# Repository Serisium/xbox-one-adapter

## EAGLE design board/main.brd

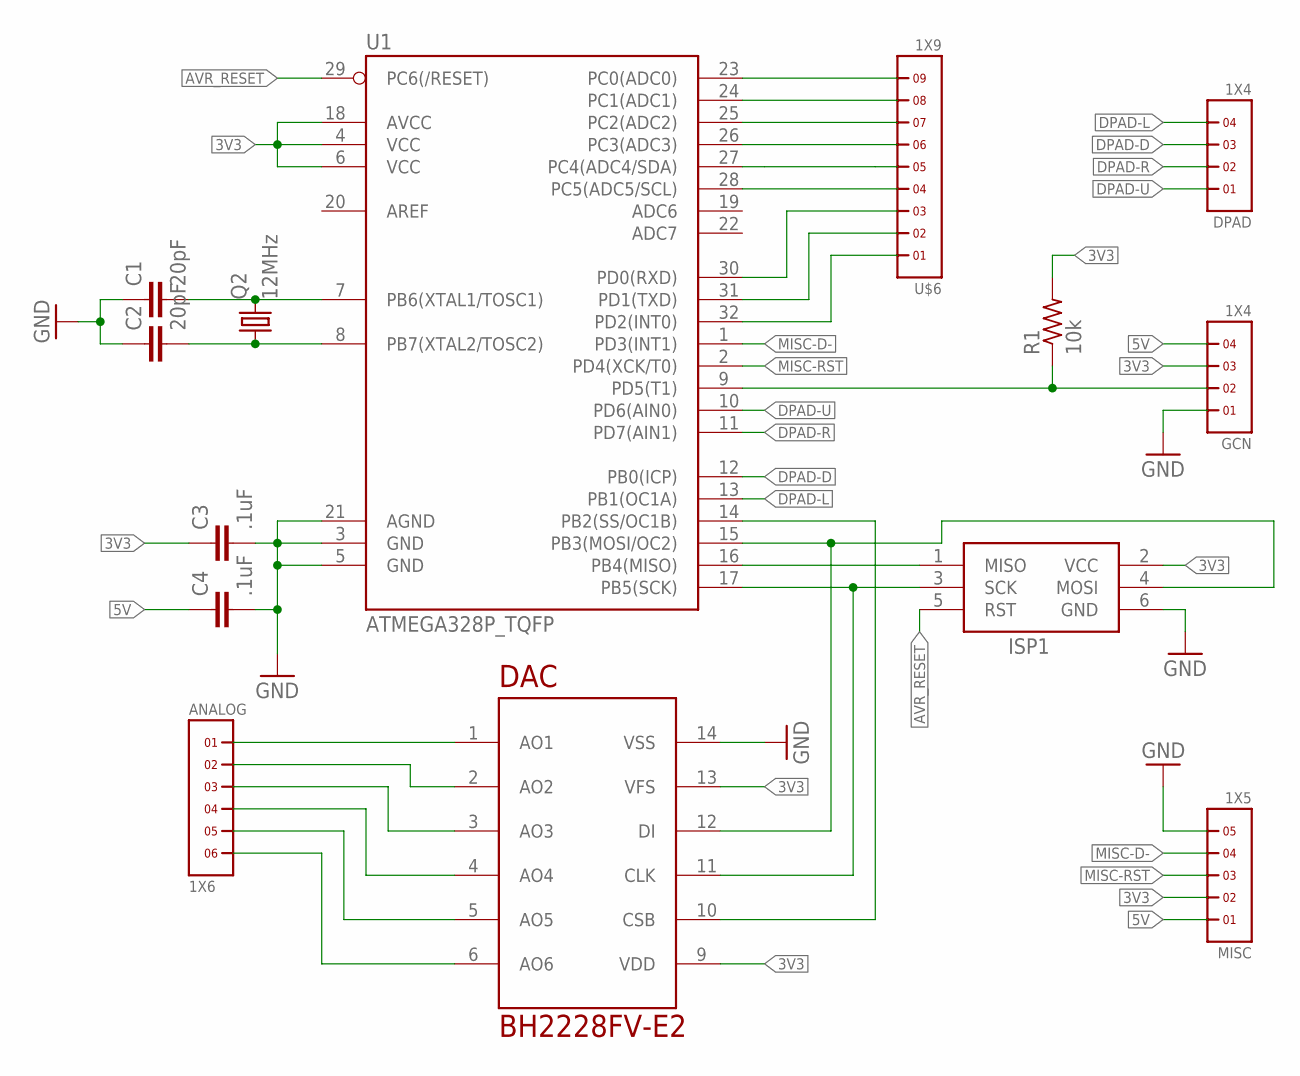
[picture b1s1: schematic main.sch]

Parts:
ANALOG: 1X6
C1, C2: 20pF; C0603
C3, C4: .1uF; C0603
DAC: BH2228FV-E2; TSSOP14
DPAD: 1X4
GCN: 1X4
ISP1: AVRISP-6; AVRISP
MISC: 1X5
Q2: 12MHz; HC49/S
R1: 10k; R0603
U1: ATMEGA328P_TQFP; TQFP32-08
U$6: 1X9

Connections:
3V3: C3.1, DAC.9 (VDD), DAC.13 (VFS), GCN.3, ISP1.2 (VCC), MISC.2, R1.2, U1.4 (VCC), U1.6 (VCC), U1.18 (AVCC)
5V: C4.1, GCN.4, MISC.1
A: U1.23 (PC0(ADC0)), U$6.9
AVR_RESET: ISP1.5 (RST), U1.29 (PC6(/RESET))
B: U1.24 (PC1(ADC1)), U$6.8
DPAD-D: DPAD.3, U1.12 (PB0(ICP))
DPAD-L: DPAD.4, U1.13 (PB1(OC1A))
DPAD-R: DPAD.2, U1.11 (PD7(AIN1))
DPAD-U: DPAD.1, U1.10 (PD6(AIN0))
GCN_SIG: GCN.2, R1.1, U1.9 (PD5(T1))
GND: C1.1, C2.1, C3.2, C4.2, DAC.14 (VSS), GCN.1, ISP1.6 (GND), MISC.5, U1.3 (GND), U1.5 (GND), U1.21 (AGND)
L: U1.27 (PC4(ADC4/SDA)), U$6.5
MENU: U1.30 (PD0(RXD)), U$6.3
MISC-D-: MISC.4, U1.1 (PD3(INT1))
MISC-RST: MISC.3, U1.2 (PD4(XCK/T0))
MOSI: DAC.12 (DI), ISP1.4 (MOSI), U1.15 (PB3(MOSI/OC2))
unnamed: C1.2, Q2.2, U1.7 (PB6(XTAL1/TOSC1))
unnamed: C2.2, Q2.1, U1.8 (PB7(XTAL2/TOSC2))
unnamed: ISP1.1 (MISO), U1.16 (PB4(MISO))
R: U1.28 (PC5(ADC5/SCL)), U$6.4
SCK: DAC.11 (CLK), ISP1.3 (SCK), U1.17 (PB5(SCK))
SS: DAC.10 (CSB), U1.14 (PB2(SS/OC1B))
VIEW: U1.32 (PD2(INT0)), U$6.1
X: U1.25 (PC2(ADC2)), U$6.7
X1: ANALOG.1, DAC.1 (AO1)
X2: ANALOG.4, DAC.4 (AO4)
XBOX: U1.31 (PD1(TXD)), U$6.2
Y: U1.26 (PC3(ADC3)), U$6.6
Y1: ANALOG.2, DAC.2 (AO2)
Y2: ANALOG.5, DAC.5 (AO5)
Z1: ANALOG.3, DAC.3 (AO3)
Z3: ANALOG.6, DAC.6 (AO6)

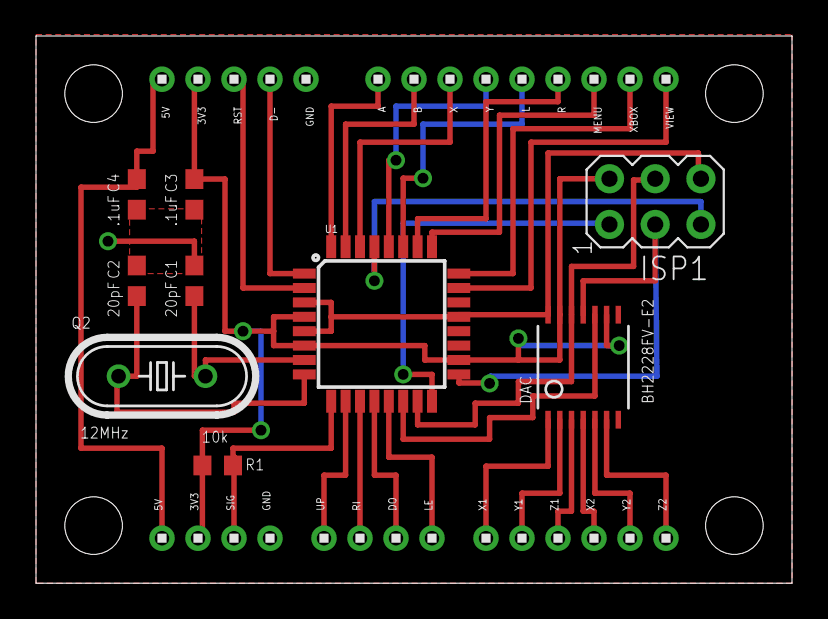
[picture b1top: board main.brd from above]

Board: 2 copper layers, 42.0 x 30.4 mm, 14 parts (0 on the bottom side), 32 nets.

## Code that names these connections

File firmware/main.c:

#include <stdint.h>
#include <avr/wdt.h>
#include <avr/interrupt.h>
#include <util/delay.h>

#include "xbox.h"
#include "pins.h"
#include "controller.h"
#include "spi.h"

int main(void)
{
    wdt_enable(WDTO_1S);    // enable 1s watchdog timer

    // Enable external interrupt on INT0(PD2) rising edge
    //EICRA = (1 << ISC01) | (1 << ISC00);    // INT0 Rising edge
    //EIMSK = (1 << INT0);                    // Enable INT0

    // Enable interrupts
    //sei();
    cli();

    // Set BIT_DEBUG as debug output line
    SET_BIT(DDR_DEBUG, BIT_DEBUG);

    // Set pins high
    PORTB = 0xFF;
    PORTC = 0xFF;
    PORTD = 0xFF;

    // Set XBox interface pins as output
    DDRB = (1<<PB0) || (1<<PB1);
    DDRC = (1<<PC0) || (1<<PC1) || (1<<PC2) || (1<<PC3) || (1<<PC4) || (1<<PC5);
    DDRD = (1<<PD0) || (1<<PD1) || (1<<PD2) || (1<<PD3) || (1<<PD4) || (1<<PD6) || (1<<PD7);

    // Set up SPI for analog outputs, ch 19.5 in datasheet
    // Enable SS, MOSI, and SCK as outputs
    SET_BIT(DDRB, PB2); // SS
    SET_BIT(DDRB, PB3); // MOSI
    SET_BIT(DDRB, PB5); // SCK
    // Set latch as idle-high
    SET_BIT(PORTB, PB2);
    // Enable SPI in Master mode, with a rate of F_CPU/64
    SPCR = (1<<SPE)|(1<<MSTR)|(1<<SPR1);

    uint8_t controller_buffer[8] = {0};
    Controller *controller = (Controller*)controller_buffer;
    uint8_t cal_buffer[8] = {0};
    Calibration_Constants *calibration_constants = (Calibration_Constants*)cal_buffer;

    uint8_t idle_buffer[8] = {0x00, 0x80, 0x80, 0x80, 0x80, 0x80, 0xFF, 0xFF};
    Controller *idle = (Controller*)idle_buffer;

    //init_calibration(idle, calibration_constants);

    uint8_t is_connected = 0;
    uint8_t disconnected_count = 0;
    uint8_t connected_count = 0;

    while(1) {
        wdt_reset();

        for(uint8_t i = 0; i < 8; ++i) {
            controller_buffer[i] = 0x00;
        }

		gc_poll(controller_buffer);

        // The 1st bit of the 2nd byte is gauranteed to be a "1", so we can
        // use it to detect a connected controller
        if(controller_buffer[1] != 0) {
            // Reset the disconnected_count debounce buffer
            disconnected_count = 0;

            // Branch if we've been connected, or if this is a new connection
            if(is_connected) {
                apply_calibration(controller, calibration_constants);
                xbox_send(controller);
            } else {
                if(connected_count >= 10) {
                    is_connected = 1;
                    init_calibration(controller, calibration_constants);
                    xbox_send(controller);
                } else {
                    connected_count++;
                    xbox_send(idle);
                }
            }
        } else {    // Otherwise, no controller is connected
            connected_count = 0;
            // See if the controller was previously connected
            if(is_connected == 1) {
                // If so, debounce it for 10 pulses(40ms)
                disconnected_count++;
                if(disconnected_count > 10) {
                    // Then, reset by timing out the watchdog timer
                    wdt_enable(WDTO_15MS);
                    for(;;){}
                }
            }
            xbox_send(idle);
        }

        _delay_us(3300);
    }
}

// Watch the USB D- line for activity, so we can stay synchronized
/*
ISR(INT0_vect) {
    // Wait out a sync pulse's duration
    _delay_us(15);

    // Clear the interrupt flag, so we won't double-trigger on previous pulses
    SET_BIT(EIFR, INTF0);

    // Wait out another 2us, to give INTF0 a chance to trigger
    _delay_us(2);

    // See if there's more activity on D-
    // If so, this is a data transfer. If not, it was just a sync pulse
    if(GET_BIT(EIFR, INTF0)) {
        // Toggle the debug line
        SET_BIT(PORT_DEBUG, BIT_DEBUG);
        _delay_us(20);
        CLEAR_BIT(PORT_DEBUG, BIT_DEBUG);
    }
}
*/

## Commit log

2016-10-02 Added left/right states
2016-10-05 Added analog scan on BH2228FV channel A1
2016-10-09 Added inline ASM to poll controller
2016-10-09 Added basic controller reading loop
2016-10-10 Finished initial controller polling in C
2016-10-10 Added analog adapter functions
2016-10-10 fixed inverted Y axis
2016-10-10 Fixed out of bounds checking
2016-10-17 Rewrote analog routine to use controller struct
2016-10-17 Added basic digital presses
2016-10-20 Added digital inputs
2016-10-20 Restructured project for circuit directory
2016-10-20 Added schematic and initial part positions
2016-10-20 Finished routing
2016-10-22 Completed v0.1 of PCB
2016-11-23 Modified code for SMD setup
2016-11-23 Added automatic analog calibration
2016-12-02 Added calibration and other things
2016-12-12 Changed direct screw holes to heat-tapped threaded inserts
2016-12-20 Ready to order v0.2 boards
2017-01-07 getting three more adapters to dan

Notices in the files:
parts and their libraries:
SparkFun-DigitalIC: Licensing: Creative Commons ShareAlike 4.0 International - https://creativecommons.org/licenses/by-sa/4.0
